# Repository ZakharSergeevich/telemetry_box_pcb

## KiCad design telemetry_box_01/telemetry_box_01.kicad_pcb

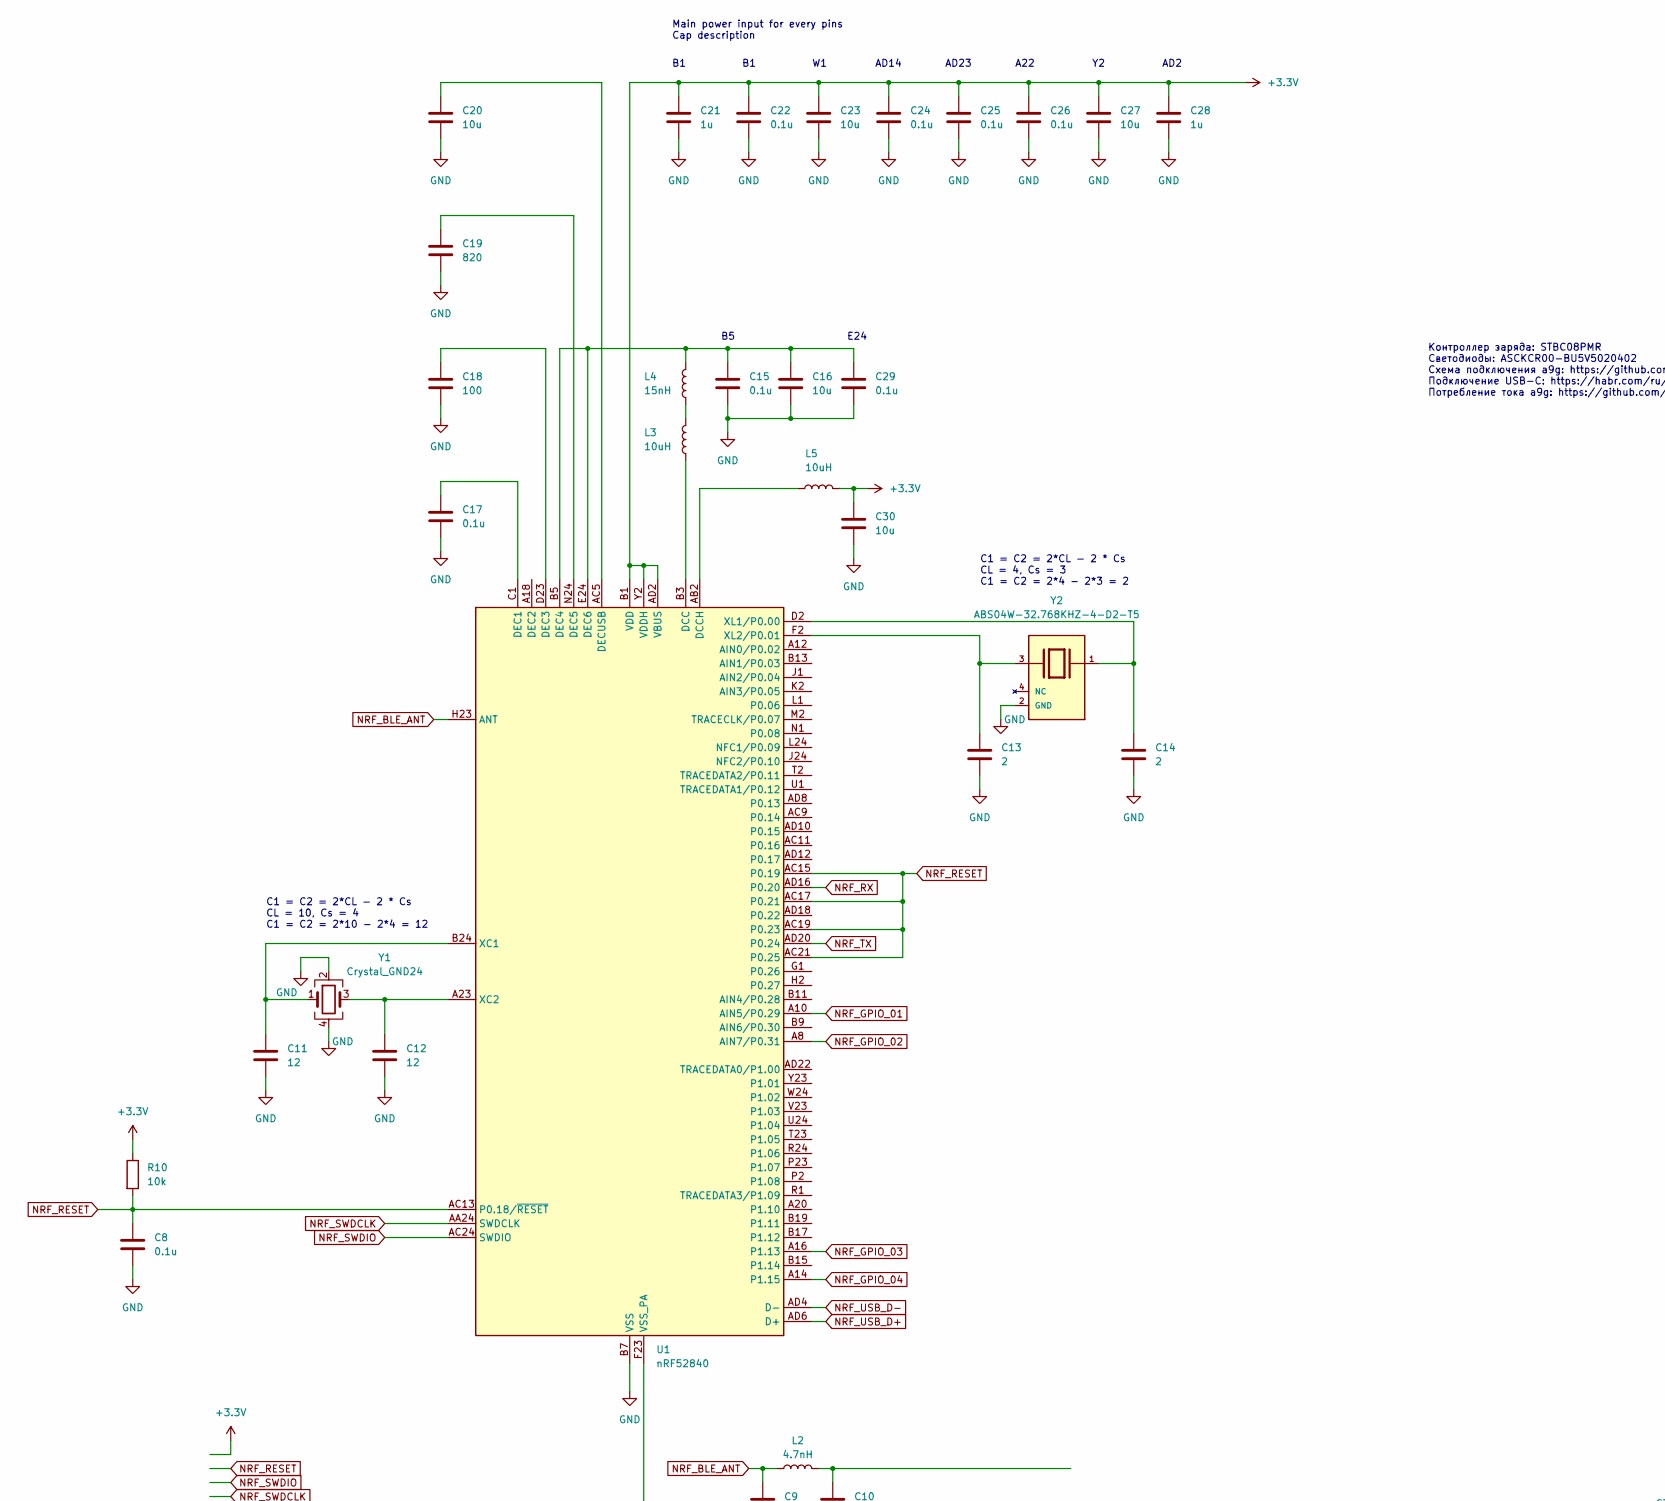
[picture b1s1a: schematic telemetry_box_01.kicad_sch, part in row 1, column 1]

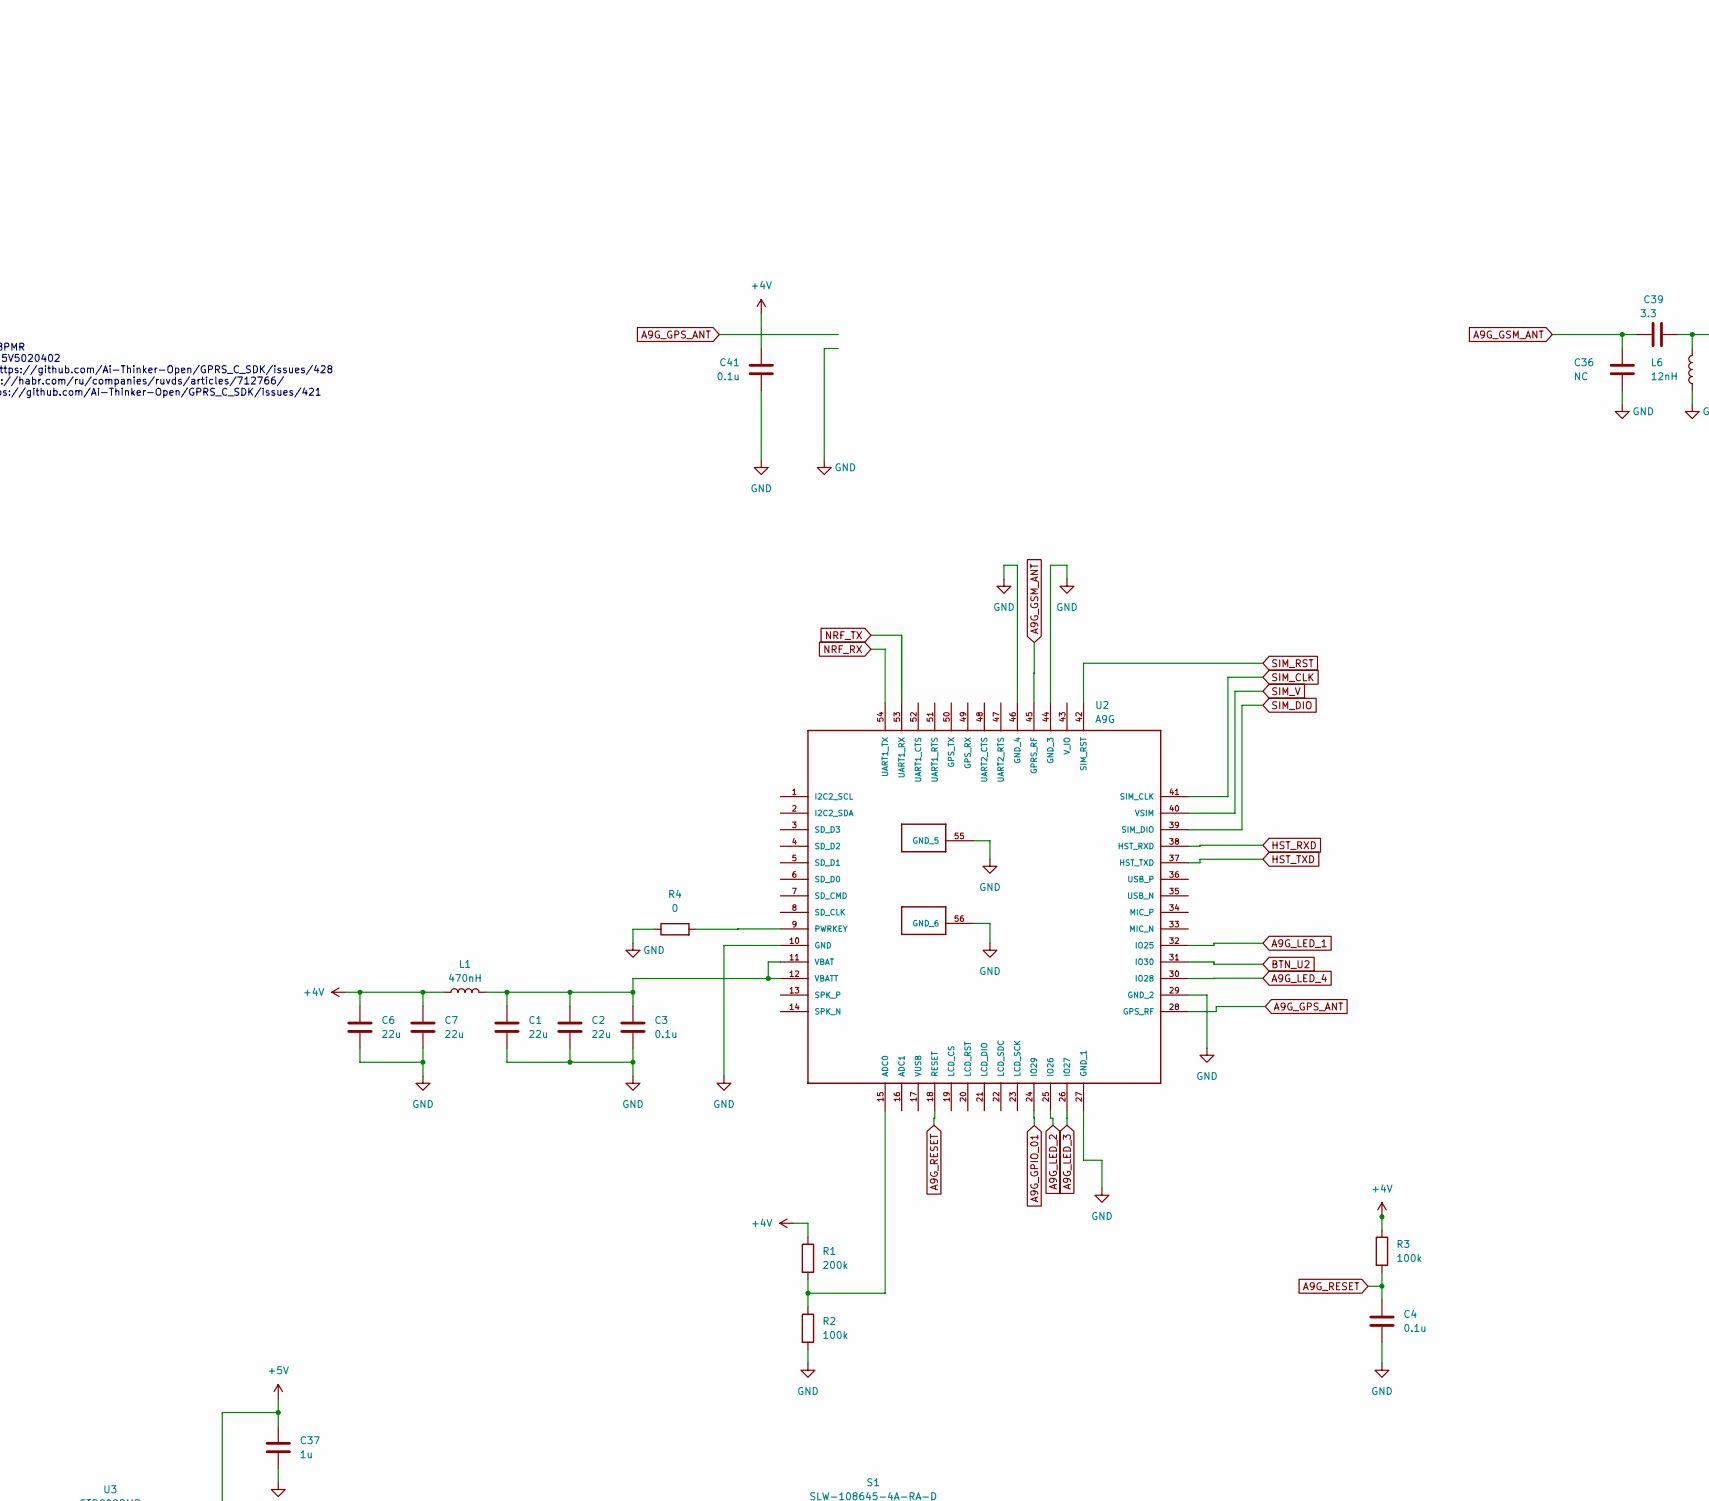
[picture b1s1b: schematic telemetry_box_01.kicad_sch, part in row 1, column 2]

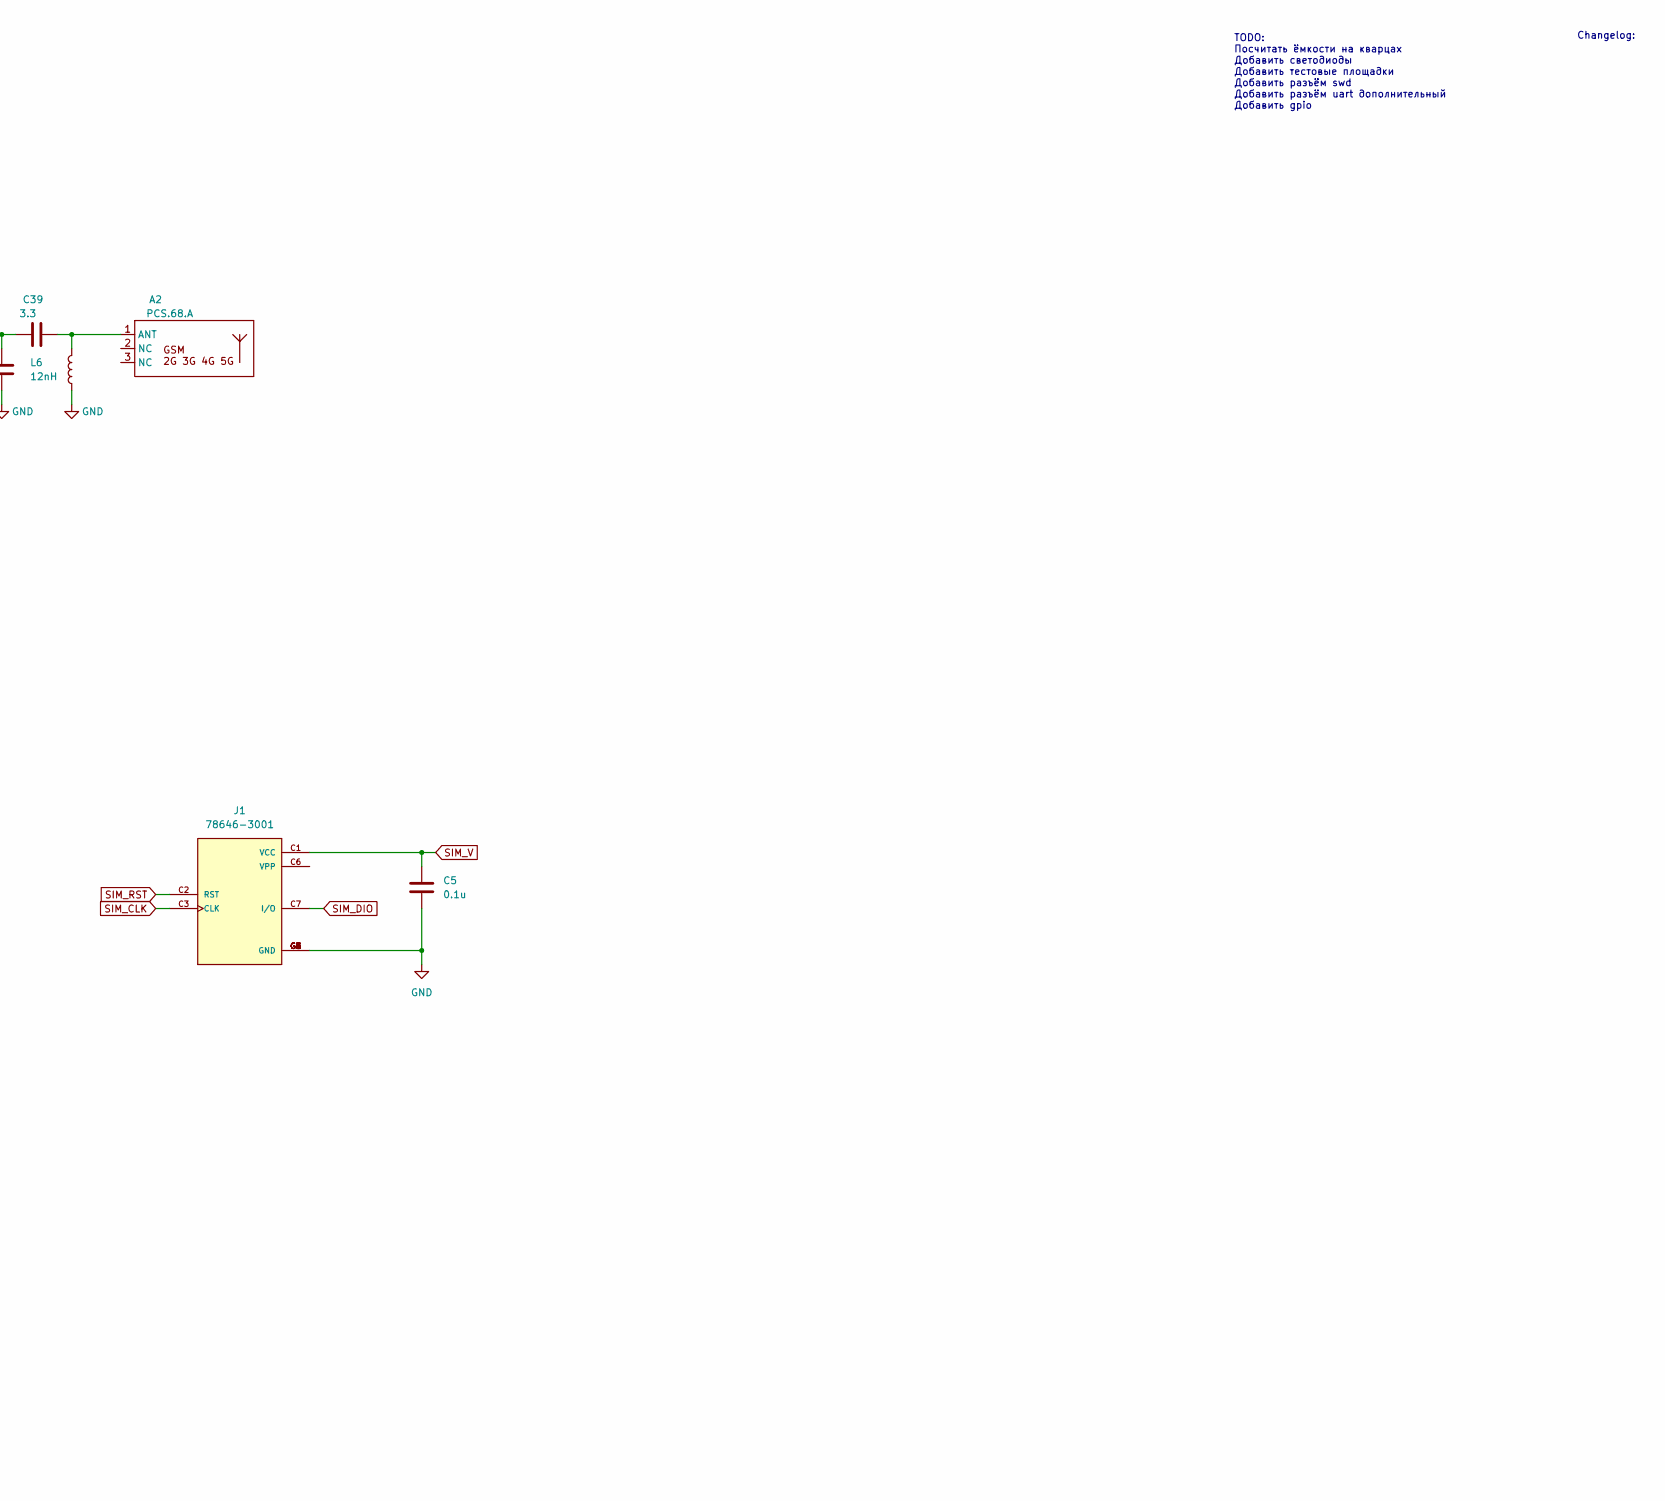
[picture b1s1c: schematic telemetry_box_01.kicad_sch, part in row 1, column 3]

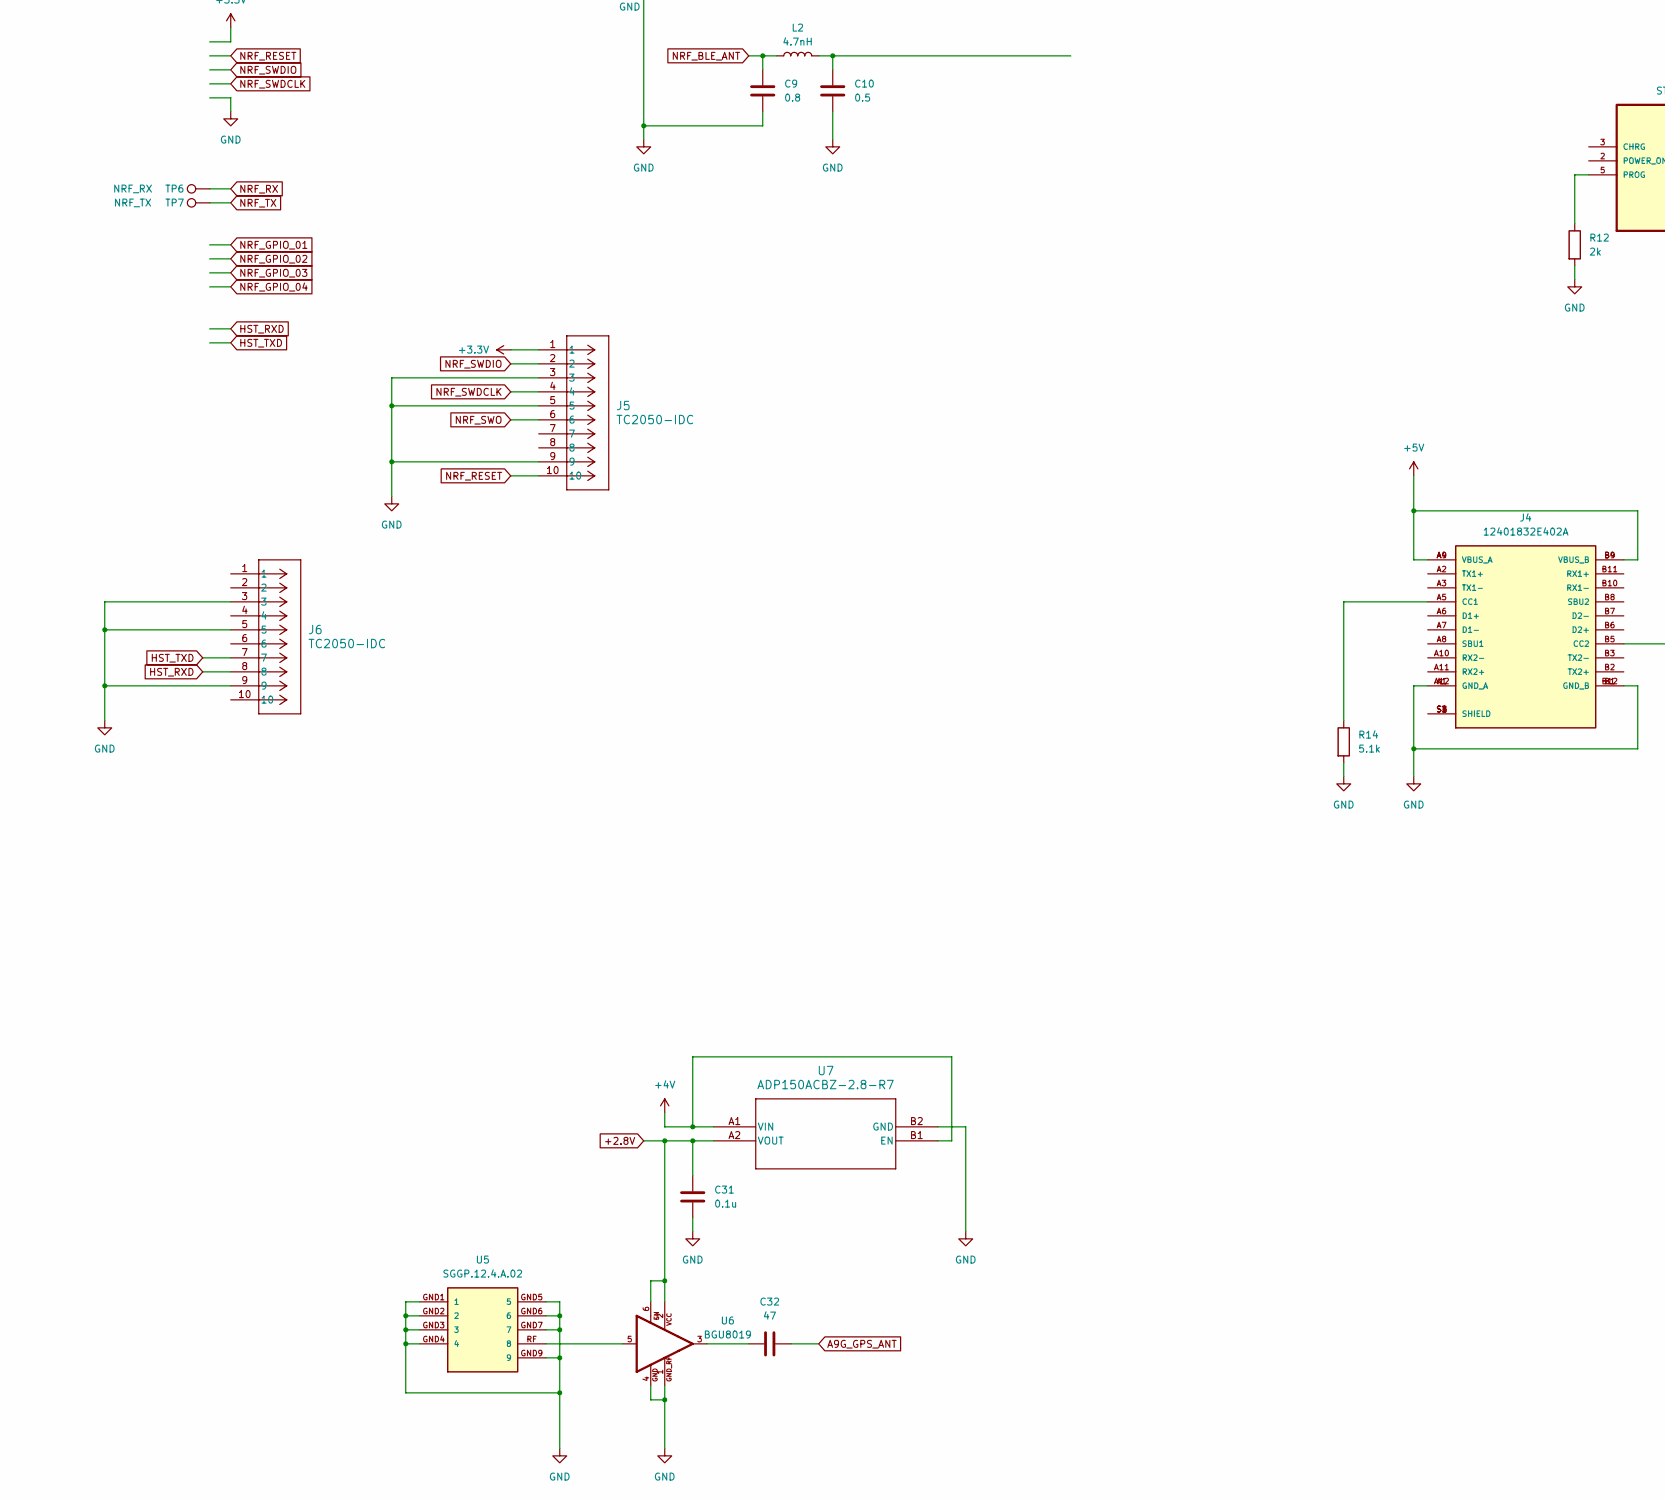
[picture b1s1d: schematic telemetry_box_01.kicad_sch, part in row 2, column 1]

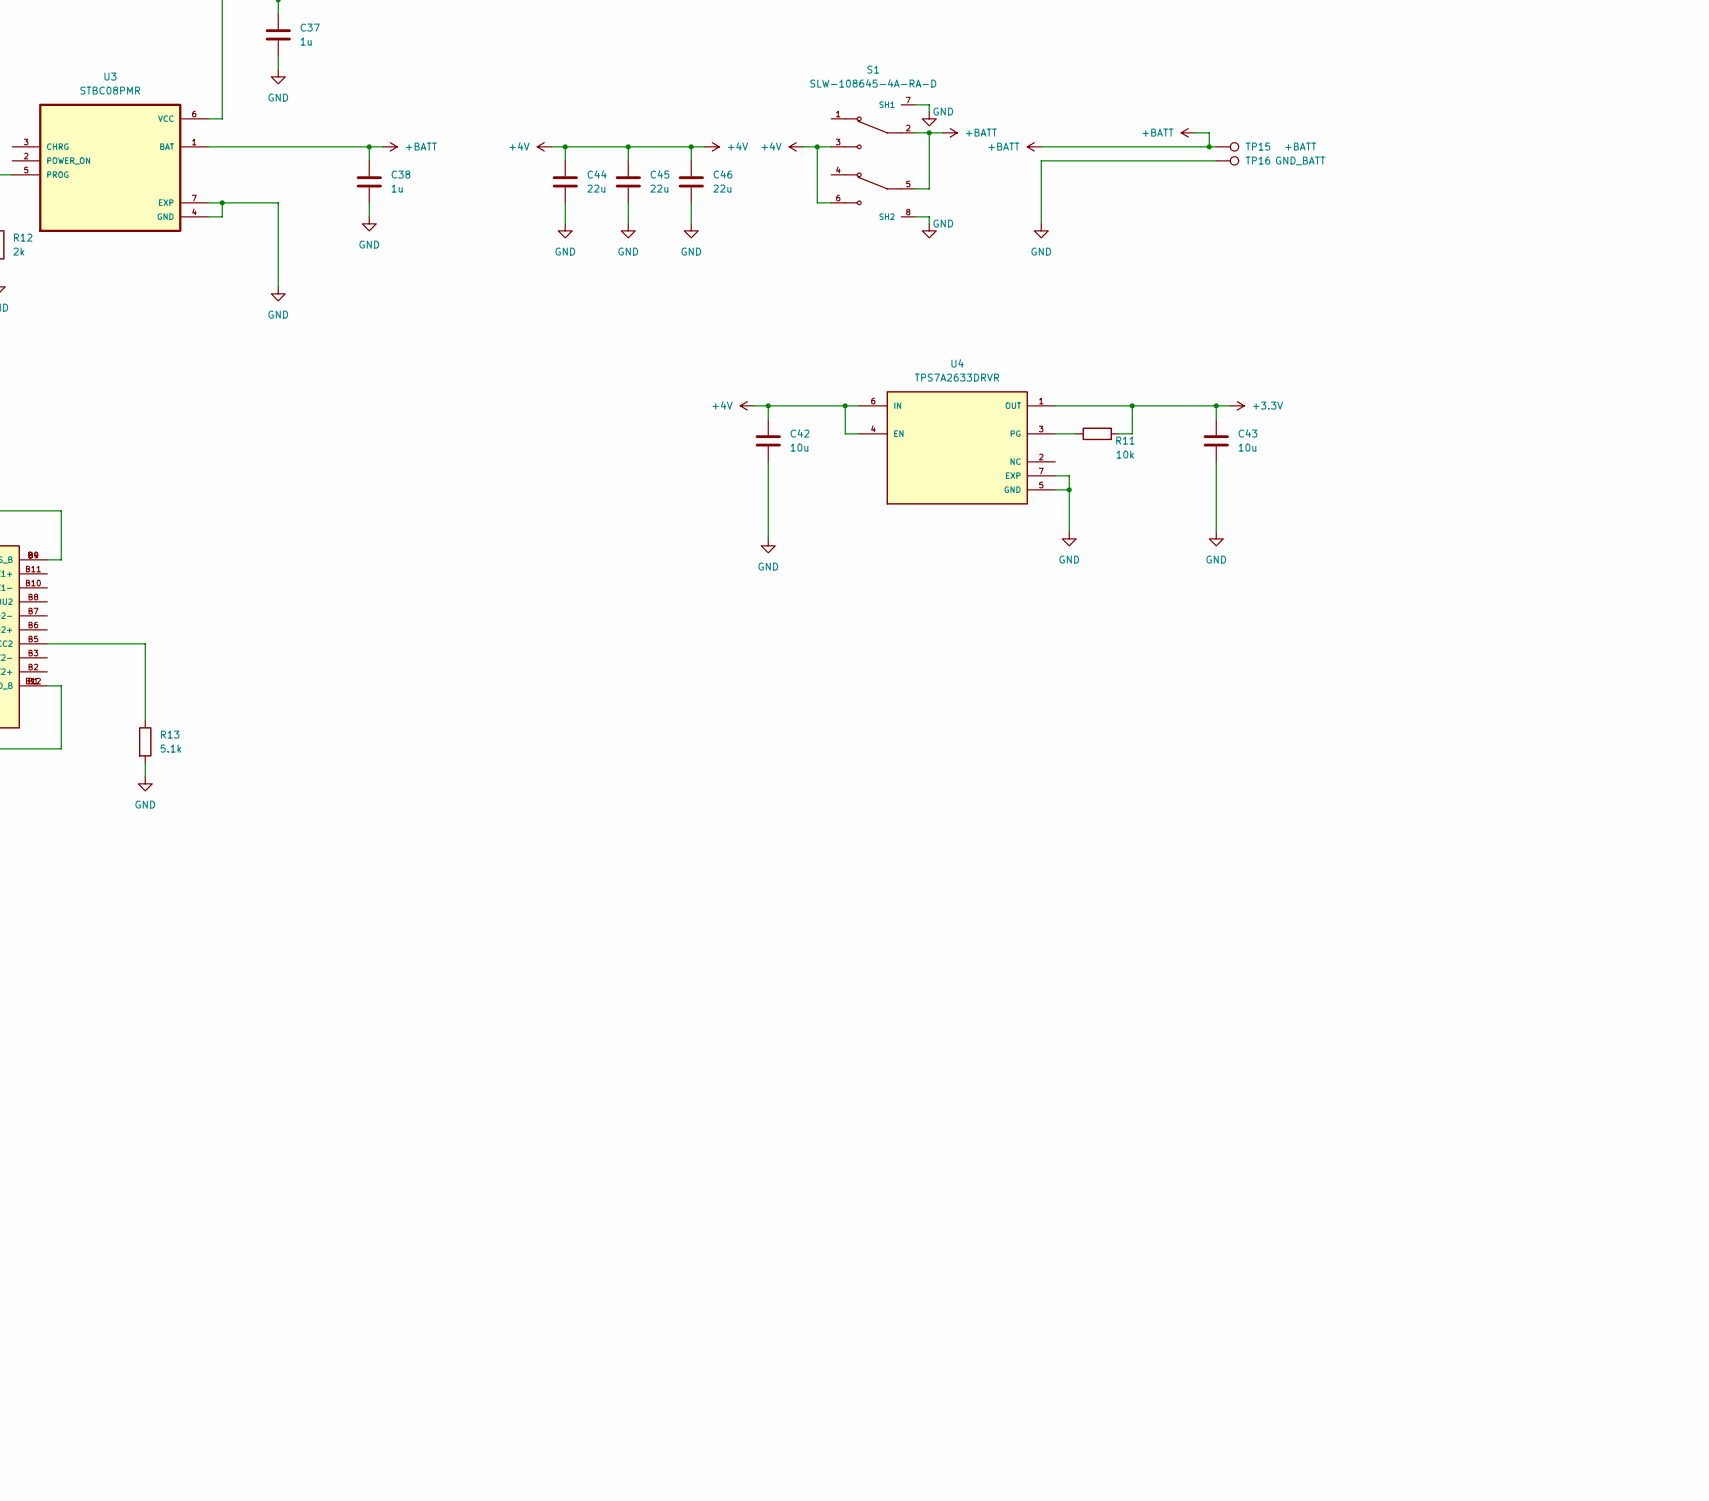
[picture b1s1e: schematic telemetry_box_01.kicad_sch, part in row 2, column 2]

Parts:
A2: PCS.68.A
C1, C2, C6, C7, C44, C45, C46: 22u; C_0603_1608Metric
C3, C4, C5, C8, C15, C17, C22, C24, C25, C26, C29, C31, C41: 0.1u; C_0201_0603Metric
C9: 0.8; C_0201_0603Metric
C10: 0.5; C_0201_0603Metric
C11, C12: 12; C_0201_0603Metric
C13, C14: 2; C_0201_0603Metric
C16, C20, C23, C27, C30, C42, C43: 10u; C_0402_1005Metric
C18: 100; C_0201_0603Metric
C19: 820; C_0201_0603Metric
C21, C28, C37, C38: 1u; C_0402_1005Metric
C32: 47; C_0201_0603Metric
C36: NC; C_0402_1005Metric
C39: 3.3; C_0402_1005Metric
J1: 78646-3001; MOLEX_78646-3001; DIGI-KEY_PART_NUMBER WM9364CT-ND
J4: 12401832E402A; AMPHENOL_12401832E402A; PARTREV X2
J5, J6: TC2050-IDC; CONN_TC2050-IDC_TGC
L1: 470nH; L_0805_2012Metric_Pad1.15x1.40mm_HandSolder
L2: 4.7nH; L_0402_1005Metric
L3, L5: 10uH; L_0603_1608Metric
L4: 15nH; L_0402_1005Metric
L6: 12nH; L_0402_1005Metric
R1: 200k; R_0201_0603Metric
R2, R3: 100k; R_0201_0603Metric
R4: 0; R_0201_0603Metric
R10, R11: 10k; R_0201_0603Metric
R12: 2k; R_0201_0603Metric
R13, R14: 5.1k; R_0201_0603Metric
S1: SLW-108645-4A-RA-D; SW_SLW-108645-4A-RA-D; PARTREV 1.01
TP6: NRF_RX; TestPoint_Pad_D2.0mm
TP7: NRF_TX; TestPoint_Pad_D2.0mm
TP15: +BATT; TestPoint_THTPad_D2.0mm_Drill1.0mm
TP16: GND_BATT; TestPoint_THTPad_D2.0mm_Drill1.0mm
U1: nRF52840; Nordic_AQFN-73-1EP_7x7mm_P0.5mm
U2: A9G; A9
U3: STBC08PMR; SON95P300X300X100-7N; PARTREV 4
U4: TPS7A2633DRVR; SON65P200X200X80-7N
U5: SGGP.12.4.A.02
U6: BGU8019; SOT1232
U7: ADP150ACBZ-2.8-R7; CB_4_3_ADI
Y1: Crystal_GND24; Crystal_SMD_2016-4Pin_2.0x1.6mm
Y2: ABS04W-32.768KHZ-4-D2-T5; XTAL_ABS04W-32.768KHZ-4-D2-T5; PARTREV 12.18.2018

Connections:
+2.8V: C31.1, U6.2, U6.6, U7.A2 (VOUT)
+3.3V: C21.1, C22.1, C23.1, C24.1, C25.1, C26.1, C27.1, C28.1, C30.1, C43.1, J5.1, L5.2, R10.1, R11.2, U1.A22 (VDD), U1.AD2 (VBUS), U1.AD14 (VDD), U1.AD23 (VDD), U1.B1 (VDD), U1.W1 (VDD), U1.Y2 (VDDH), U4.1 (OUT)
+4V: C6.1, C7.1, C41.1, C42.1, C44.1, C45.1, C46.1, L1.1, R1.1, R3.1, S1.3, S1.6, U4.4 (EN), U4.6 (IN), U7.A1 (VIN), U7.B1 (EN)
+5V: C37.1, J4.A4 (VBUS_A), J4.A9 (VBUS_A), J4.B4 (VBUS_B), J4.B9 (VBUS_B), U3.6 (VCC)
+BATT: C38.1, S1.2, S1.5, TP15.1, U3.1 (BAT)
A9G_GPIO_01: U2.24 (IO29)
A9G_GPS_ANT: C32.2, U2.28 (GPS_RF)
A9G_GSM_ANT: C36.1, C39.1, U2.45 (GPRS_RF)
A9G_LED_1: U2.32 (IO25)
A9G_LED_2: U2.25 (IO26)
A9G_LED_3: U2.26 (IO27)
A9G_LED_4: U2.30 (IO28)
A9G_RESET: C4.1, R3.2, U2.18 (RESET)
BTN_U2: U2.31 (IO30)
GND: C1.2, C2.2, C3.2, C4.2, C5.2, C6.2, C7.2, C8.2, C9.2, C10.2, C11.2, C12.2, C13.2, C14.2, C15.2, C16.2, C17.2, C18.2, C19.2, C20.2, C21.2, C22.2, C23.2, C24.2, C25.2, C26.2, C27.2, C28.2, C29.2, C30.2, C31.2, C36.2, C37.2, C38.2, C41.2, C42.2, C43.2, C44.2, C45.2, C46.2, J1.C5 (GND), J1.G1 (GND), J1.G2 (GND), J1.G3 (GND), J1.G4 (GND), J1.G5 (GND), J1.G6 (GND), J4.A1 (GND_A), J4.A12 (GND_A), J4.B1 (GND_B), J4.B12 (GND_B), J5.3, J5.5, J5.9, J6.3, J6.5, J6.9, L6.1, R2.2, R4.1, R12.2, R13.2, R14.2, S1.7 (SH1), S1.8 (SH2), TP16.1, U1.B7 (VSS), U1.EP (VSS), U1.F23 (VSS_PA), U2.10 (GND), U2.27 (GND_1), U2.29 (GND_2), U2.44 (GND_3), U2.46 (GND_4), U2.55 (GND_5), U2.56 (GND_6), U3.4 (GND), U3.7 (EXP), U4.5 (GND), U4.7 (EXP), U5.GND1 (1), U5.GND2 (2), U5.GND3 (3), U5.GND4 (4), U5.GND5 (5), U5.GND6 (6), U5.GND7 (7), U5.GND9 (9), U6.1, U6.4, U7.B2 (GND), Y1.2, Y1.4, Y2.2 (GND)
HST_RXD: J6.8, U2.38 (HST_RXD)
HST_TXD: J6.7, U2.37 (HST_TXD)
NRF_BLE_ANT: C9.1, L2.1, U1.H23 (ANT)
NRF_GPIO_01: U1.A10 (AIN5/P0.29)
NRF_GPIO_02: U1.A8 (AIN7/P0.31)
NRF_GPIO_03: U1.A16 (P1.13)
NRF_GPIO_04: U1.A14 (P1.15)
NRF_RESET: C8.1, J5.10, R10.2, U1.AC13 (P0.18/~RESET), U1.AC15 (P0.19), U1.AC17 (P0.21), U1.AC19 (P0.23), U1.AC21 (P0.25)
NRF_RX: TP6.1, U1.AD16 (P0.20), U2.54 (UART1_TX)
NRF_SWDCLK: J5.4, U1.AA24 (SWDCLK)
NRF_SWDIO: J5.2, U1.AC24 (SWDIO)
NRF_SWO: J5.6
NRF_TX: TP7.1, U1.AD20 (P0.24), U2.53 (UART1_RX)
NRF_USB_D+: U1.AD6 (D+)
NRF_USB_D-: U1.AD4 (D-)
unnamed: A2.1 (ANT), C39.2, L6.2
unnamed: C10.1, L2.2
unnamed: C32.1, U6.3
unnamed: J4.A5 (CC1), R14.1
unnamed: J4.B5 (CC2), R13.1
unnamed: J4.S1 (SHIELD), J4.S2 (SHIELD), J4.S3 (SHIELD), J4.S4 (SHIELD)
unnamed: L3.2, L4.1
unnamed: L3.1, U1.B3 (DCC)
unnamed: L5.1, U1.AB2 (DCCH)
unnamed: C17.1, U1.C1 (DEC1)
unnamed: C18.1, U1.D23 (DEC3)
unnamed: C15.1, C16.1, C29.1, L4.2, U1.B5 (DEC4), U1.E24 (DEC6)
unnamed: C19.1, U1.N24 (DEC5)
unnamed: C20.1, U1.AC5 (DECUSB)
unnamed: C11.1, U1.B24 (XC1), Y1.1
unnamed: C12.1, U1.A23 (XC2), Y1.3
unnamed: C14.1, U1.D2 (XL1/P0.00), Y2.1
unnamed: C13.1, U1.F2 (XL2/P0.01), Y2.3
unnamed: R1.2, R2.1, U2.15 (ADC0)
unnamed: R4.2, U2.9 (PWRKEY)
unnamed: C1.1, C2.1, C3.1, L1.2, U2.11 (VBAT), U2.12 (VBATT)
unnamed: R12.1, U3.5 (PROG)
unnamed: R11.1, U4.3 (PG)
unnamed: U5.RF (8), U6.5
SIM_CLK: J1.C3 (CLK), U2.41 (SIM_CLK)
SIM_DIO: J1.C7 (I/O), U2.39 (SIM_DIO)
SIM_RST: J1.C2 (RST), U2.42 (SIM_RST)
SIM_V: C5.1, J1.C1 (VCC), U2.40 (VSIM)

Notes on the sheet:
C1 = C2 = 2*CL - 2 * Cs CL = 4, Cs = 3 C1 = C2 = 2*4 - 2*3 = 2
Changelog:
A22
C1 = C2 = 2*CL - 2 * Cs CL = 10, Cs = 4 C1 = C2 = 2*10 - 2*4 = 12
E24
Main power input for every pins Cap description
AD14
AD23
TODO: Посчитать ёмкости на кварцах Добавить светодиоды Добавить тестовые площадки Добавить разъём swd Добавить разъём uart дополнительный Добавить gpio
AD2
Контроллер заряда: STBC08PMR Светодиоды: ASCKCR00-BU5V5020402 Схема подключения a9g: https://github.com/Ai-Thinker-Open/GPRS_C_SDK/issues/428 Подключение USB-C: https://habr.com/ru/companies/ruvds/articles/712766/ Потребление тока a9g: https://github.com/Ai-Thinker-Open/GPRS_C_SDK/issues/421

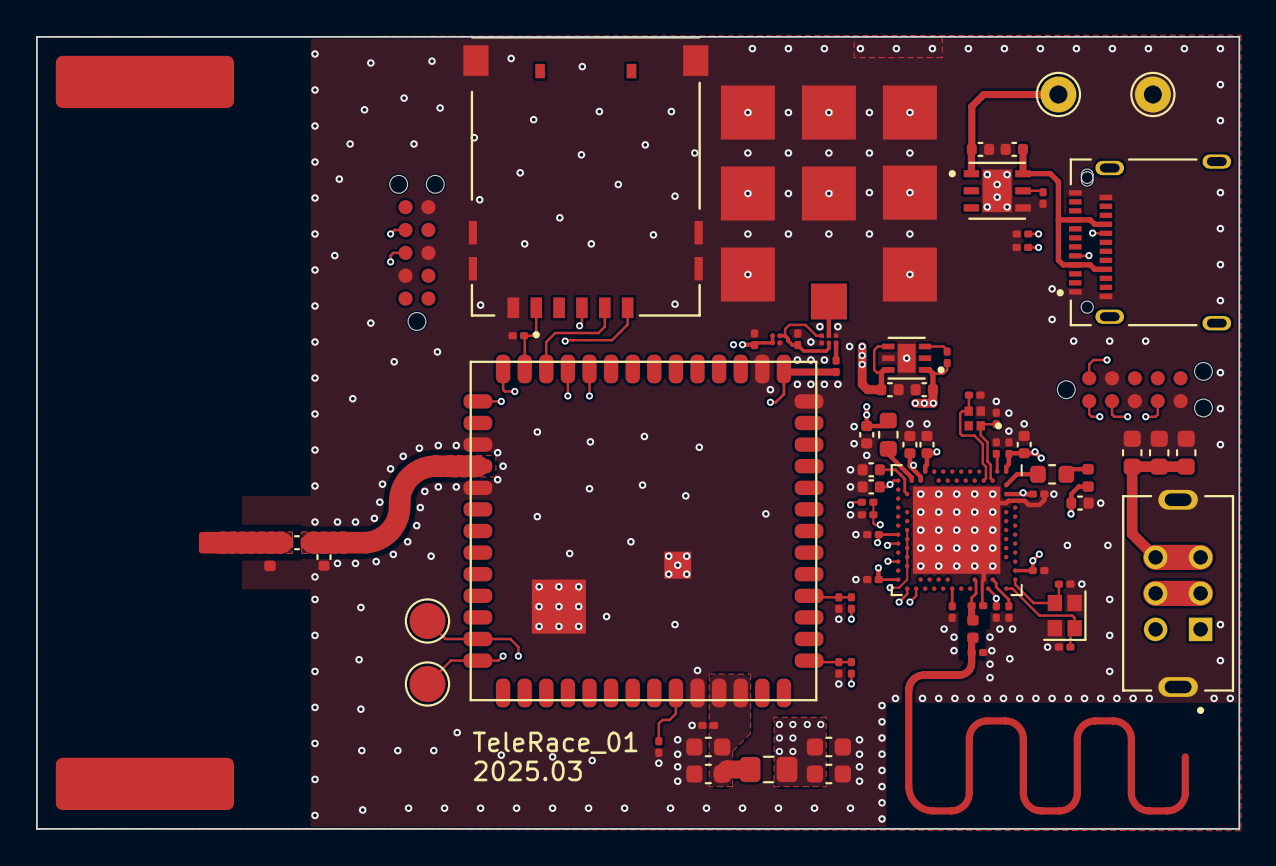
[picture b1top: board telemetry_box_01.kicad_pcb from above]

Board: 4 copper layers, 66.8 x 44.0 mm, 76 parts (0 on the bottom side), 45 nets.

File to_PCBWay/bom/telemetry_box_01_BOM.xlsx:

Item # | *Designator | *Qty | Manufacturer | *Mfg Part # | Description / Value | *Package/Footprint | Type | Your Instructions / Notes
1 | A2 | 1 | Taoglas | PCS.68.A | Antennas PCS.68.A Wideband 5G/4G PCB SMD Antenna | 42mm * 10mm | SMD
2 | C1, C2, C6, C7, C44, C45, C46 | 7 | Samsung Electro-Mechanics | CL10A226MO7JZNC | Multilayer Ceramic Capacitors MLCC - SMD/SMT 22uF+/-20% 16V X5R 1 0603 | 603 | SMD
3 | C3, C4, C5, C8, C15, C17, C22, C24, C25, C26, C29, C31, C41 | 13 | Samsung Electro-Mechanics | CL03A104KA3NNNC | Multilayer Ceramic Capacitors MLCC - SMD/SMT 100nF+/-10% 25V X5R 0201 | 201 | SMD
4 | C9 | 1 | Murata | GRM0335C1HR80BA01D | Multilayer Ceramic Capacitors MLCC - SMD/SMT 0.8 pF 50 VDC 0.1 pF 0201 C0G (NP0) | 201 | SMD
5 | C10 | 1 | Murata | GRM0335C1ER50BA01D | Multilayer Ceramic Capacitors MLCC - SMD/SMT 0.5 pF 25 VDC 0.1 pF 0201 C0G (NP0) | 201 | SMD
6 | C11, C12 | 2 | Murata | GRM0335C1E120GA01D | Multilayer Ceramic Capacitors MLCC - SMD/SMT 12 pF 25 VDC 2% 0201 C0G (NP0) | 201 | SMD
7 | C13, C14 | 2 | Murata | GRM0335C1E2R0BA01D | Multilayer Ceramic Capacitors MLCC - SMD/SMT 2 pF 25 VDC 0.1 pF 0201 C0G (NP0) | 201 | SMD
8 | C16, C20, C23, C27, C30, C42, C43 | 7 | Samsung Electro-Mechanics | CL05A106MP5NUNC | Multilayer Ceramic Capacitors MLCC - SMD/SMT 10uF+/-20% 10V X5R 1005 | 402 | SMD
9 | C18 | 1 | Murata | GRM0335C1E101JA01D | Multilayer Ceramic Capacitors MLCC - SMD/SMT 100 pF 25 VDC 5% 0201 C0G (NP0) | 201 | SMD
10 | C32 | 1 | Murata | GRM0335C1E470FA01D | Multilayer Ceramic Capacitors MLCC - SMD/SMT 47 pF 25 VDC 1% 0201 C0G (NP0) | 201 | SMD
11 | C19 | 1 | Murata | GRM0335C1E821JA01D | Multilayer Ceramic Capacitors MLCC - SMD/SMT 820 pF 25 VDC 5% 0201 C0G (NP0) | 201 | SMD
12 | C21, C28, C37, C38 | 4 | Samsung Electro-Mechanics | CL05A105KO5NNNC | Multilayer Ceramic Capacitors MLCC - SMD/SMT 1uF+/-10% 16V X5R 10 0402 | 402 | SMD
13 | C36 | 1 | no | no | no
14 | C39 | 1 | Murata | GRM1555C1H3R3CA01D | Multilayer Ceramic Capacitors MLCC - SMD/SMT 3.3 pF 50 VDC 0.25 pF 0402 C0G (NP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 | 402 | SMD
15 | J1 | 1 | Molex | 78646-3001 | Memory Card Connectors MICRO SIM CON ASSY 1.45HT PUSHPULL 6CKT
16 | J4 | 1 | Amphenol | 12401832E402A | USB Connectors USB TYPE C RCPT R/A top mount dual SMT
17 | L1 | 1 | Murata | DFE201210U-R47M=P2 | Power Inductors - SMD .47 UH 3.0A | 805 | SMD
18 | L2 | 1 | Murata | LQW15AN4N7B00D | RF Inductors - SMD 4.7 NH +-.1NH | 402 | SMD
19 | L3, L5 | 2 | Murata | LQM18DH100M70L | Power Inductors - SMD Fixed IND 10uH 300mA POWRTRN | 603 | SMD
20 | L4 | 1 | Murata | LQW15AN15NJ00D | RF Inductors - SMD 15 NH 5% | 402 | SMD
21 | L6 | 1 | Murata | LQW15AN12NJ00D | RF Inductors - SMD 12 NH 5% | 402 | SMD
22 | R1 | 1 | YAGEO | RC0201FR-07200KL | Thick Film Resistors - SMD 200 kOhms 50mW 0201 1% | 201 | SMD
23 | R2, R3 | 2 | YAGEO | RC0201FR-07100KL | Thick Film Resistors - SMD 100 kOhms 50mW 0201 1% | 201 | SMD
24 | R4 | 1 | YAGEO | RC0201FR-070RL | Thick Film Resistors - SMD 0 Ohms 50mW 0201 1% | 201 | SMD
25 | R10, R11 | 2 | YAGEO | RC0201FR-7D10KL | Thick Film Resistors - SMD 10 kOhms 50 mW 0201 1% | 201 | SMD
26 | R12 | 1 | YAGEO | RC0201FR-072KL | Thick Film Resistors - SMD 2 kOhms 50mW 0201 1% | 201 | SMD
27 | R13, R14 | 2 | YAGEO | RC0201FR-075K1L | Thick Film Resistors - SMD 5.1 kOhms 50 mW 0201 1% | 201 | SMD
28 | S1 | 1 | Same Sky | SLW-108645-4A-RA-D | Slide Switches 10.8 x 6.4 x 5 mm, 4 mm Raised Slide Actuator, Right-Angle, Thro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 |  | DIP
29 | U1 | 1 | Nordic Semiconductor | nRF52840-QIAA-R | RF System on a Chip - SoC nRF52840-QIAA QFN 73L 7x7 | AQFN-73
30 | U2 | 1 |  | A9G | A9G
31 | U3 | 1 | STMicroelectronics | STBC08PMR | Battery Management 800mA Linear Li Ion batery chargr
32 | U4 | 1 | Texas Instruments | TPS7A2633DRVR | LDO Voltage Regulators 500-mA, 18-V, ultra-low-IQ, high-accuracy, adjustable lo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
33 | U5 | 1 | Taoglas | SGGP.12.4.A.02 | Antennas SGGP.12.4.A.02 GPS/GLONASS/Galileo 12*12*4mm SMD Mount Patch |  | SMD
34 | U6 | 1 | NXP | BGU8019X | RF Amplifier Low Noise Amplifier MMIC for GPS |  | SMD
35 | U7 | 1 | Analog Devices | ADP150ACBZ-2.8-R7 | Linear Voltage Regulators 150mA LDO 2.8Vout | WLCSP-4 | SMD
36 | Y1 | 1 | ABRACON | ABM11-32.000MHZ-B7G-T | Crystals CRYSTAL 32.0000MHZ 10PF SMD | 2mm * 1.6mm
37 | Y2 | 1 | ABRACON | ABS04W-32.768KHZ-4-D2-T5 | Crystals CRYSTAL 32.768KHZ 4PF SMD | 1.2mm * 1mm

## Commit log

2023-10-28 feat(board): EMI protected PCB
2023-10-28 fix(vias): blind vias have been removed to optimize production
2023-10-28 docs(production): gerber, BOM, position files for PCBWay
2025-03-20 feat(board): optimization of component placement -reduce product dimensions -remove GPS antenna -add power to the SMA connector for external GPS antenna -move debug pins -replace ble smd antenna with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
2025-04-04 feat(board): installation GPS antenna, power switch, tag-connect on PCB
2025-06-04 fix(production): gerber, BOM, position files for PCBWay -successful production of modules
